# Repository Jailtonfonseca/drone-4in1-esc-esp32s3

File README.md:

# Drone — 4×ESC trifásico + ESP32-S3 na mesma PCB

> ✅ **Estado real (2026-10-12):** o board corrente é a **v10 ROTEADA** —
> [`fase3_pcb/v10/v10_roteada.kicad_pcb`](fase3_pcb/v10/v10_roteada.kicad_pcb) —
> e passa em **TODOS os gates G1–G8** do verificador
> ([`fase3_pcb/v10/verificacao_v10.txt`](fase3_pcb/v10/verificacao_v10.txt)):
> **0 curtos** (o gate novo G8 pegou 354 violações que a roteagem anterior tinha),
> 0 pads fora do contorno, 0 nets órfãs, 0 vias em keepout, 173/173 zonas preenchidas,
> 0 pads GND/VBAT_PROT sem via de stitch, ocupação elétrica 23,4 %. O pipeline de
> roteamento (FreeRouting 1.9.0) agora exporta o cobre das nets excluídas como
> **keepouts** — a placa é fabricável. Registro central de erros e correções:
> [`ERROS_CONHECIDOS.md`](ERROS_CONHECIDOS.md) (§9 = auditoria de 12/10). A BOM corrente é a
> [`orcamento/BOM_FABRICACAO_v10.csv`](orcamento/BOM_FABRICACAO_v10.csv) (MOSFET
> `NVMFS6H824NT1G`, 24 un — a BOM antiga mandava comprar o FET errado).

Projeto de **uma única PCB** que concentra: 4 inversores trifásicos (ESC), gate drivers,
sensoriamento de corrente, MCU com WiFi (ESP32-S3), IMU, barômetro, USB e toda a regulação
de energia a partir de pack LiPo 6S (25,2 V máx / 19,8 V mín).

Todo o projeto foi feito **100 % headless** nesta máquina (Linux aarch64, sem desktop):
script + CLI + PNG, com KiCad 5.1.9 via `pcbnew` (Python), ngspice 34, Icarus Verilog 11,
Yosys 0.9, gerbv 2.7.0, FreeRouting 1.9.0 (Java 17 + Xvfb) e matplotlib.

> **Regra de honestidade do projeto:** todo número afirmado nos relatórios vem de um arquivo
> de log gerado de verdade por uma ferramenta executada nesta máquina, e cada afirmação tem
> etiqueta de origem (`[MEDIDO]`, `[CALC]`, `[DATASHEET]`, `[PREMISSA]`, `[EST]`). Nada foi
> estimado "no papel" e apresentado como medido. "Pronto" é propriedade do artefato:
> [`verificacoes/verifica_projeto.py`](verificacoes/verifica_projeto.py) faz asserções duras
> e exit 1 com a lista exata do que falta.

---

## ⚠️ Status: projeto EM ANDAMENTO

| Fase | Escopo | Estado |
|---|---|---|
| 0 | Especificação e dimensionamento | ✅ concluída |
| 1 | Esquema elétrico (8 figuras) | ✅ concluída |
| 2 | Simulação SPICE + PWM em Verilog | ✅ concluída |
| 3 | PCB (6 camadas) + roteamento | ⚠️ **board v10 roteado, G1–G8 todos OK, 0 curtos** — **134/151** nets de sinal roteadas; 17 air-wires restantes (o núcleo congestionado de potência: `I_M###`, `HOM###`, `VBM###`, `LOM###`, `IMU_CS/INT`, `CC2`, `GLM103`, `UART_TX`, `VBUS_USB`) |
| 4 | Entrega: montagem, teste, riscos, regulatório | ✅ **documentação escrita** — os 4 documentos de `fase4_entrega/` existem e acompanham o envio (F14 = "já escrito", `plano/WP2_FABRICACAO.md` §1 item 11). O que falta é **executar** a bancada (G3), não escrevê-la |

**A placa v10 roteada está livre de curtos e gates verdes** — o estado
de "pronto da Fase 3" é checado por asserções duras:
[`verificacoes/verifica_projeto.py`](verificacoes/verifica_projeto.py) (SES com wires>0,
nets 100 % roteadas, G1–G8 na base E no roteado, BOM com preço em toda linha comprável).
Ele reprova exatamente no que falta — hoje: **as 17 air-wires** do núcleo de potência
(ganho marginal do autorroteador é ~1 net/30 min nesse regime; recomendação:
roteamento manual no KiCad ou revisão v11 do layout para aliviar a congestão).
Rodá-lo a qualquer momento diz onde o projeto está, sem impressão de sessão.

Para a ordem de execução completa do projeto, do estado atual até o primeiro voo —
o que falta para fabricar, o que falta para voar, a sequência de etapas, os gates e as
decisões pendentes — ver **[`PLANO_FINAL.md`](PLANO_FINAL.md)**.

### Avisos importantes

- **Nada foi validado em bancada.** Os limites de corrente contínua e o comportamento
  térmico do projeto são `[PREMISSA]` até a execução de `fase4_entrega/PLANO_TESTE_BANCADA.md`.
- **Antes de voar:** requisitos regulatórios brasileiros (registro/SISANT, peso, distância)
  precisam ser verificados — ver `fase4_entrega/SEGURANCA_E_REGULATORIO.md`.
- LiPo 6S tem energia suficiente para incêndio. Ver `fase4_entrega/RISCOS.md`.

---

## Estrutura do repositório

```
drone/
├── ERROS_CONHECIDOS.md              # registro central de erros (§9 = auditoria 12/10)
├── AUDITORIA_ERROS_2026-10-04.md    # relatório da 1a auditoria (~110 erros)
├── PROMPT_AGENTE_DRONE.md           # briefing original do projeto
├── verificacoes/                    # asserções duras de projeto (verifica_projeto.py)
├── datasheets/                      # datasheets usados (ESP32-S3-WROOM-1 etc.)
├── fase0_especificacao/             # Fase 0 — especificação
├── fase1_esquema/                   # Fase 1 — esquema elétrico (PNG + geradores Python)
├── fase2_simulacao/                 # Fase 2 — SPICE (ngspice) + Verilog (PWM/dead-time)
├── fase3_pcb/                       # Fase 3 — PCB KiCad + pipeline FreeRouting (v1 … v10)
├── fase4_entrega/                   # Fase 4 — documentação de entrega
├── orcamento/                       # Orçamento de componentes (nacional e importação)
└── plano/                           # Plano de execução — WP1..WP5, DO_PROJETO e scripts
```

### Fase 0 — Especificação (`fase0_especificacao/`)

- `FASE0_ESPECIFICACAO.md` — documento principal da especificação.
- `dimensionamento_fase0.py` / `.json` / `_saida.txt` — cálculo dos estágios.
- `verifica_limites_entrada*.py` / `verifica_limites_saida*.txt` — verificação de limites.
- `lista_componentes_fase0.csv` — **lista de componentes (43 linhas)**; é a fonte de
  quantidades do orçamento.
- `diagrama_blocos_v3.py` / `diagrama_blocos_fase0_v3.png` — diagrama de blocos.

### Fase 1 — Esquema (`fase1_esquema/`)

Oito figuras geradas por código (schemdraw), cada uma com o script que a produz:

| Figura | Assunto |
|---|---|
| `esq1_entrada_protecao.png` | Entrada, proteção e anti-inversão de polaridade |
| `esq2_buck12v.png` | Buck 12 V |
| `esq3_buck5v.png` | Buck 5 V |
| `esq4_buck3v3.png` | Buck 3,3 V |
| `esq4_esc_trifasico.png` | Ponte trifásica (uma fase) |
| `esq5_esc_halfbridge.png` | Half-bridge + gate driver |
| `esq6_esc_visao_geral.png` | Visão geral do ESC 4× |
| `esq7_mcu.png` | MCU ESP32-S3 |
| `esq8_arvore_energia.png` | Árvore de energia |

Scripts: `gera_fase1_a.py`, `gera_fase1_b.py`, `gera_fase1_c.py`, `gera_esq4.py`,
`gera_esquemas_p1.py` (rascunhos em `rascunho/`).

### Fase 2 — Simulação (`fase2_simulacao/`)

- `RESULTADOS_FASE2_SPICE.md` — relatório (uma linha por grandeza, com valor esperado,
  medido, erro e chave no log).
- `resultados_fase2_spice.csv` — a mesma tabela em CSV.
- Netlists: `buck12.cir`, `buck5.cir`, `buck3v3.cir`, `divisor_vbat.cir`, `shunt_amp.cir`,
  `gate_drive.cir`, `prot_inversao.cir`, `bemf_div.cir` (+ `.log` de cada).
- `gera_tabela.py`, `minimiza_ripple.py` — automação e otimização.
- `verilog/RELATORIO_VERILOG.md` — PWM de 12 canais com dead-time em Verilog, simulado com
  Icarus e sintetizado com Yosys.
- `_testes/` — netlists de diagnóstico usadas durante a investigação.

### Fase 3 — PCB (`fase3_pcb/`)

- `gera_pcb_v1.py` … `gera_pcb_v10.py` — geradores do board (o board é gerado por código;
  a linhagem viva é a v10 — as anteriores são registro histórico).
- `freerouting/` — pipeline de roteamento real (FreeRouting 1.9.0):
  - `dsn_export.py` — board → DSN, **com keepouts do cobre das nets excluídas** (§9.1)
    e **wires fixos** das rotas existentes (para completar roteamento parcial);
  - `ses_import.py` — SES → trilhas KiCad (com guarda anti-re-import);
  - `SesFromFrb.java` — extrai o SES de um `.frb` intermediário sem GUI (§9.6);
  - `fr_watchdog.py` — dispensa diálogos modais do FR dentro do Xvfb;
  - `FONTE_FREEROUTING.md` — o runbook: tudo medido, não presumido.
- `verifica_fase3_v10.py` → `v10/verificacao_v10.txt` — os **gates G1–G8**
  (G8 = trilha×cobre de net excluída, o gate dos 354 curtos).
- `v10/` — board base (`v10_drone.kicad_pcb`), **board roteado** (`v10_roteada.kicad_pcb`),
  SES final, logs do run e verificação.
- `verificacoes/verifica_projeto.py` (na raiz do repo) — asserções duras de projeto inteiro.
- `kicad-cli` não existe nesta máquina: os Gerbers são gerados por script `pcbnew`.

### Fase 4 — Entrega (`fase4_entrega/`)

- `PLANO_TESTE_BANCADA.md` — instrumentos e ensaios, com o que medir e critério de aceite.
- `MONTAGEM_ORDEM_DE_SOLDA.md` — ordem de solda e cuidados de montagem.
- `SEGURANCA_E_REGULATORIO.md` — segurança elétrica e requisitos regulatórios (Brasil).
- `RISCOS.md` — matriz severidade × probabilidade, mitigação e detecção.
- `ANALISE_WIFI_CONTROLE.md` — análise do link de controle WiFi.
- `calcs_fase4.txt`, `calcs_wifi_controle.txt` — saídas de cálculo usadas nos documentos.

### Orçamento (`orcamento/`)

- `ORCAMENTO.md` — relatório completo (cenário A: compra nacional; cenário B: importação).
- `orcamento_detalhado.csv` — item a item.
- `orcamento_por_bloco.csv` — agrupado por bloco funcional.
- `custo_por_bloco.png` — gráfico.
- `orcamento.py` — script que gera tudo acima.

As quantidades vêm de `fase0_especificacao/lista_componentes_fase0.csv`. Itens sem cotação
real coletada estão marcados `[EST]` no relatório.

### Plano de execução (`plano/`)

- `WP1_ROTEAMENTO.md` a `WP5_DECISOES.md` — as cinco auditorias consolidadas.
- `DO_PROJETO.md`, `mede_v7_wp1.py` — definition of done e a contagem independente do layout.
- A ordem de trabalho única está em [`PLANO_FINAL.md`](PLANO_FINAL.md), na raiz.

---

## Reproduzir

Nada aqui precisa de desktop. Exemplo:

```sh
# simulação SPICE
cd fase2_simulacao && ngspice -b buck12.cir

# board base v10 (requer KiCad 5.1 com módulo pcbnew do sistema)
cd fase3_pcb && python3.9 gera_pcb_v10.py

# pipeline de roteamento (FreeRouting 1.9.0 + Java 17 + Xvfb; ver FONTE_FREEROUTING.md)
cd fase3_pcb/freerouting && cp freerouting.json /tmp/     # o FR lê do java.io.tmpdir!
python3.9 dsn_export.py ../v10/v10_drone.kicad_pcb ../v10/freerouting_run/v10_dsn_input.dsn
xvfb-run -a java -jar <caminho>/freerouting-1.9.0.jar \
    -de ../v10/freerouting_run/v10_dsn_input.dsn -do ../v10/freerouting_run/v10_final.ses
python3.9 ses_import.py ../v10/v10_drone.kicad_pcb \
    ../v10/freerouting_run/v10_final.ses ../v10/v10_roteada.kicad_pcb

# verificação (gates G1-G8) e asserções duras de projeto
python3.9 fase3_pcb/verifica_fase3_v10.py fase3_pcb/v10/v10_roteada.kicad_pcb
python3.9 verificacoes/verifica_projeto.py

# orçamento
cd orcamento && python3.9 orcamento.py
```

## Licença

Distribuído sob a **licença MIT** — texto completo em [`LICENSE`](LICENSE).

A licença cobre todo o conteúdo do repositório: o software (scripts Python e Verilog),
os arquivos de projeto (esquemas, layout KiCad, Gerbers) e a documentação.

Como toda licença permissiva, a MIT é fornecida **"como está", sem garantia de qualquer
espécie**. Isso pesa aqui mais que o normal: este é um projeto de eletrônica de potência
**em andamento e não validado em bancada**, então a ausência de garantia e a limitação de
responsabilidade valem integralmente (ver os avisos no topo deste README).

> **Nota sobre os datasheets:** os PDFs em `datasheets/` são material de terceiros
> (Espressif, TDK/InvenSense), incluídos apenas como referência de projeto e **não**
> são cobertos pela licença MIT deste repositório.

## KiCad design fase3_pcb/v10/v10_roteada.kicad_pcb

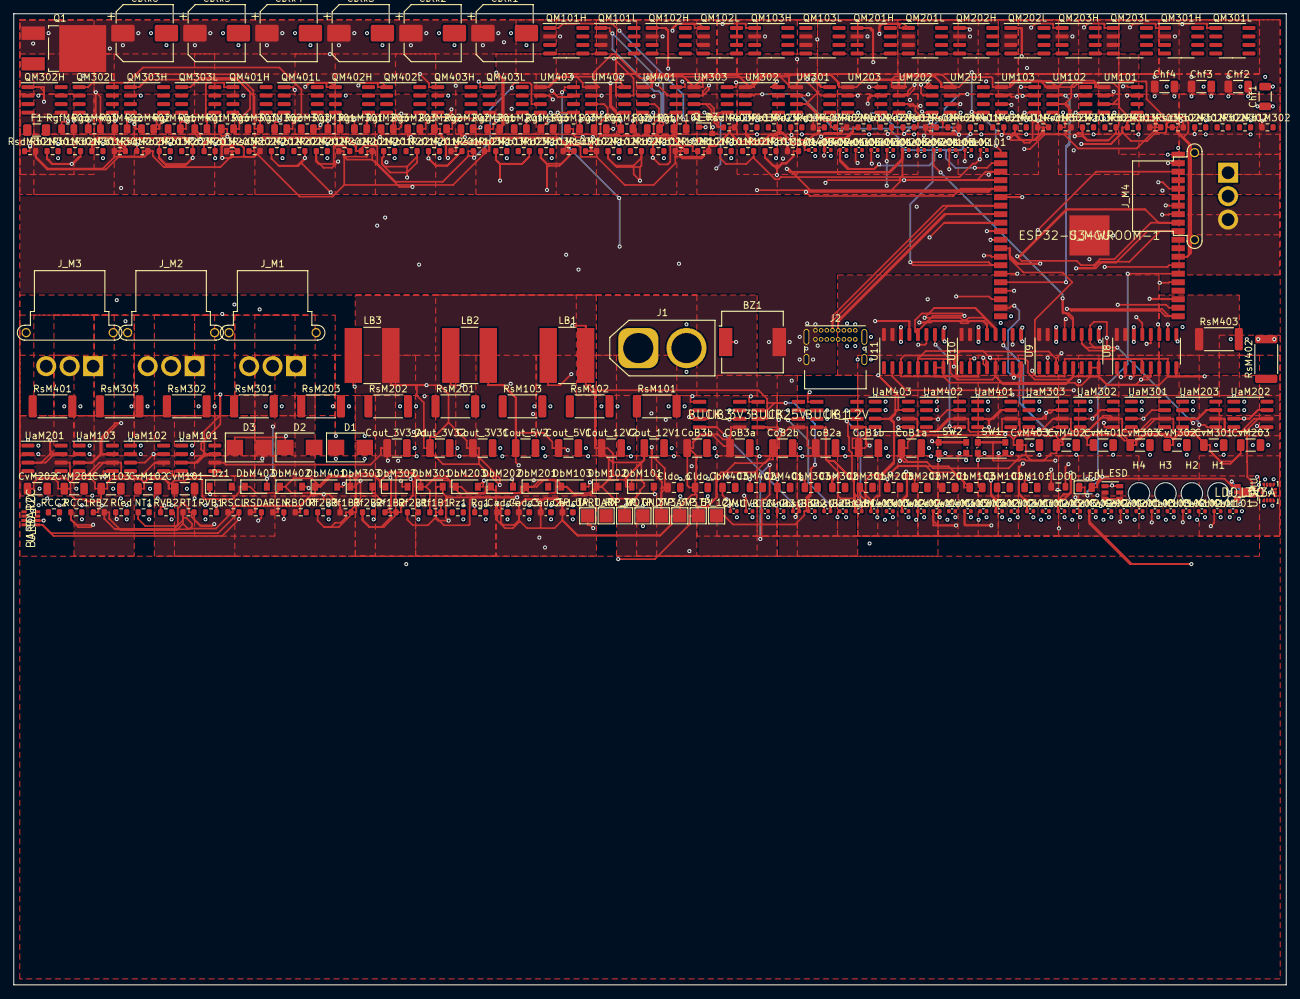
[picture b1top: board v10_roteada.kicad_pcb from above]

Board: 6 copper layers, 190.0 x 145.0 mm, 319 parts (0 on the bottom side), 179 nets.

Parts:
BZ1: Buzzer; Buzzer_CUI_CPT-9019S-SMT
CEN: C; C_0402_1005Metric
CIMU: C; C_0402_1005Metric
CVB: C; C_0402_1005Metric
CaM101, CaM102, CaM103, CaM201, CaM202, CaM203, CaM301, CaM302, CaM303, CaM401, CaM402, CaM403: C; C_0402_1005Metric
Cadc1, Cadc2, Cadc3, Cadc4: C; C_0603_1608Metric
CbM101, CbM102, CbM103, CbM201, CbM202, CbM203, CbM301, CbM302, CbM303, CbM401, CbM402, CbM403: C; C_0805_2012Metric
CbeM101, CbeM102, CbeM103, CbeM201, CbeM202, CbeM203, CbeM301, CbeM302, CbeM303, CbeM401, CbeM402, CbeM403: C; C_0402_1005Metric
Cblk1, Cblk2, Cblk3, Cblk4, Cblk5, Cblk6: CP; CP_Elec_8x10
CbstB1, CbstB2, CbstB3: C; C_0402_1005Metric
CdM101, CdM102, CdM103, CdM201, CdM202, CdM203, CdM301, CdM302, CdM303, CdM401, CdM402, CdM403: C; C_0402_1005Metric
Chf1, Chf2, Chf3, Chf4: C; C_1206_3216Metric
CinB1, CinB2, CinB3: C; C_0402_1005Metric
Cldo_i: C; C_0805_2012Metric
Cldo_o: C; C_0805_2012Metric
CoB1a, CoB1b, CoB2a, CoB2b, CoB3a, CoB3b: C; C_1210_3225Metric
Cout_3V3_A1, Cout_3V31, Cout_3V32, Cout_5V1, Cout_5V2, Cout_12V1, Cout_12V2: C; C_1210_3225Metric
CvM101, CvM102, CvM103, CvM201, CvM202, CvM203, CvM301, CvM302, CvM303, CvM401, CvM402, CvM403: C; C_1206_3216Metric
D1, D2, D3: D; D_SMB
D_LED: LED; LED_0805_2012Metric
DbM101, DbM102, DbM103, DbM201, DbM202, DbM203, DbM301, DbM302, DbM303, DbM401, DbM402, DbM403: D; D_SOD-123
Dz1: D; D_SOD-123
F1: FUSE-30A-1206; Fuse_1206_3216Metric
FLDO: L; L_0805_2012Metric
H1, H2, H3, H4: MountingHole; MountingHole_3.2mm_M3
J1: AMASS; AMASS_XT60-F_1x02_P7.20mm_Vertical
J2: USB; USB_C_Receptacle_GCT_USB4085
J_M1, J_M2, J_M3, J_M4: AMASS; AMASS_MR30PW-FB_1x03_P3.50mm_Horizontal
LB1, LB2, LB3: L; L_Bourns-SRN8040_8x8.15mm
NT1: R; R_0603_1608Metric
Q1: TO-252-2; TO-252-2_TabPin1
QM101H, QM101L, QM102H, QM102L, QM103H, QM103L, QM201H, QM201L, QM202H, QM202L, QM203H, QM203L, QM301H, QM301L, QM302H, QM302L, QM303H, QM303L, QM401H, QM401L, QM402H, QM402L, QM403H, QM403L: NVMFS6H824NT1G; SOIC-8_3.9x4.9mm_P1.27mm
Q_BZ: SOT-23
RBOOT: R; R_0603_1608Metric
RBZ: R; R_0603_1608Metric
RCC1, RCC2: R; R_0603_1608Metric
REN: R; R_0603_1608Metric
RSCL: R; R_0603_1608Metric
RSDA: R; R_0603_1608Metric
RT1: R; R_0603_1608Metric
RVB1, RVB2: R; R_0603_1608Metric
Rb1M101, Rb1M102, Rb1M103, Rb1M201, Rb1M202, Rb1M203, Rb1M301, Rb1M302, Rb1M303, Rb1M401, Rb1M402, Rb1M403, Rb2M101, Rb2M102, Rb2M103, Rb2M201, Rb2M202, Rb2M203, Rb2M301, Rb2M302, Rb2M303, Rb2M401, Rb2M402, Rb2M403: R; R_0603_1608Metric
Rd1M101, Rd1M102, Rd1M103, Rd1M201, Rd1M202, Rd1M203, Rd1M301, Rd1M302, Rd1M303, Rd1M401, Rd1M402, Rd1M403, Rd2M101, Rd2M102, Rd2M103, Rd2M201, Rd2M202, Rd2M203, Rd2M301, Rd2M302, Rd2M303, Rd2M401, Rd2M402, Rd2M403: R; R_0603_1608Metric
Rf1B1, Rf1B2, Rf1B3, Rf2B1, Rf2B2, Rf2B3: R; R_0603_1608Metric
Rg1: R; R_0603_1608Metric
RgfM101, RgfM102, RgfM103, RgfM201, RgfM202, RgfM203, RgfM301, RgfM302, RgfM303, RgfM401, RgfM402, RgfM403: R; R_0805_2012Metric
RgoM101, RgoM102, RgoM103, RgoM201, RgoM202, RgoM203, RgoM301, RgoM302, RgoM303, RgoM401, RgoM402, RgoM403: R; R_0805_2012Metric
Rled: R; R_0603_1608Metric
RsM101, RsM102, RsM103, RsM201, RsM202, RsM203, RsM301, RsM302, RsM303, RsM401, RsM402, RsM403: R; R_2512_6332Metric
RsdM101, RsdM102, RsdM103, RsdM201, RsdM202, RsdM203, RsdM301, RsdM302, RsdM303, RsdM401, RsdM402, RsdM403: R; R_0603_1608Metric
Rz1: R; R_0603_1608Metric
SW1, SW2: SW; SW_Push_1P1T_NO_CK_KMR2
TP_3V3, TP_3V3A, TP_5V, TP_12V: TestPoint; TestPoint_Pad_2.0x2.0mm
TP_GND: TestPoint; TestPoint_Pad_2.0x2.0mm
TP_UART_RX: TestPoint; TestPoint_Pad_2.0x2.0mm
TP_UART_TX: TestPoint; TestPoint_Pad_2.0x2.0mm
TP_WD: TestPoint; TestPoint_Pad_2.0x2.0mm
U8, U9, U10, U11: SOIC-16; SOIC-16_3.9x9.9mm_P1.27mm
UB1: BUCK_12V
UB2: BUCK_5V
UB3: BUCK_3V3
UM101, UM102, UM103, UM201, UM202, UM203, UM301, UM302, UM303, UM401, UM402, UM403: SOIC-8; SOIC-8_3.9x4.9mm_P1.27mm
U_BARO: BARO_I2C
U_ESD: SOT-23-6
U_IMU: LGA-14; LGA-14_3x2.5mm_P0.5mm_LayoutBorder3x4y
U_LDO: LDO_3V3A
U_MCU: ESP32-S3-WROOM-1
UaM101, UaM102, UaM103, UaM201, UaM202, UaM203, UaM301, UaM302, UaM303, UaM401, UaM402, UaM403: SOIC-8; SOIC-8_3.9x4.9mm_P1.27mm

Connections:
3V3: Cadc1.1, Cadc2.1, Cadc3.1, Cadc4.1, Cldo_i.1, CoB3a.1, CoB3b.1, Cout_3V31.1, Cout_3V32.1, D_LED.2, LB3.2, RBOOT.1, RBZ.2, REN.1, RSCL.1, RSDA.1, RT1.1, Rd1M101.1, Rd1M102.1, Rd1M103.1, Rd1M201.1, Rd1M202.1, Rd1M203.1, Rd1M301.1, Rd1M302.1, Rd1M303.1, Rd1M401.1, Rd1M402.1, Rd1M403.1, Rf1B3.1, RsdM101.2, RsdM102.2, RsdM103.2, RsdM201.2, RsdM202.2, RsdM203.2, RsdM301.2, RsdM302.2, RsdM303.2, RsdM401.2, RsdM402.2, RsdM403.2, TP_3V3.1, U8.15, U8.16, U9.15, U9.16, U10.15, U10.16, U11.15, U11.16, UB3.VCC, U_LDO.EN, U_LDO.VIN, U_MCU.2
3V3_A: Cldo_o.1, Cout_3V3_A1.1, FLDO.1, TP_3V3A.1, U_LDO.VOUT, UaM101.6, UaM102.6, UaM103.6, UaM201.6, UaM202.6, UaM203.6, UaM301.6, UaM302.6, UaM303.6, UaM401.6, UaM402.6, UaM403.6
3V3_IMU: CIMU.1, FLDO.2, U_BARO.CSB, U_BARO.VDD, U_BARO.VDDIO, U_IMU.5, U_IMU.8
5V: CoB2a.1, CoB2b.1, Cout_5V1.1, Cout_5V2.1, D3.2, LB2.2, Rf1B2.1, TP_5V.1, UB2.VCC
5V_AUX: CinB3.1, D2.1, D3.1, UB3.EN, UB3.IN
12V: CinB2.1, CoB1a.1, CoB1b.1, Cout_12V1.1, Cout_12V2.1, CvM101.1, CvM102.1, CvM103.1, CvM201.1, CvM202.1, CvM203.1, CvM301.1, CvM302.1, CvM303.1, CvM401.1, CvM402.1, CvM403.1, DbM101.1, DbM102.1, DbM103.1, DbM201.1, DbM202.1, DbM203.1, DbM301.1, DbM302.1, DbM303.1, DbM401.1, DbM402.1, DbM403.1, LB1.2, Rf1B1.1, TP_12V.1, UB1.VCC, UB2.EN, UB2.IN, UM101.1, UM102.1, UM103.1, UM201.1, UM202.1, UM203.1, UM301.1, UM302.1, UM303.1, UM401.1, UM402.1, UM403.1
ADC_CS1: U8.10, U_MCU.23
ADC_CS2: U9.10, U_MCU.15
ADC_CS3: U10.10, U_MCU.33
ADC_CS4: U11.10, U_MCU.34
BOOT_N: RBOOT.2, SW1.1, U_MCU.27
BSTB1: CbstB1.1, UB1.BST
BSTB2: CbstB2.1, UB2.BST
BSTB3: CbstB3.1, UB3.BST
BUZZER: BZ1.1, Q_BZ.1, U_MCU.16
CC1: J2.A5, RCC1.1
CC2: J2.B5, RCC2.1
EN_MCU: CEN.1, REN.2, SW2.1, U_MCU.3
FBB1: Rf1B1.2, Rf2B1.1, UB1.FB
FBB2: Rf1B2.2, Rf2B2.1, UB2.FB
FBB3: Rf1B3.2, Rf2B3.1, UB3.FB
GHM101: QM101H.1, RgoM101.2
GHM102: QM102H.1, RgoM102.2
GHM103: QM103H.1, RgoM103.2
GHM201: QM201H.1, RgoM201.2
GHM202: QM202H.1, RgoM202.2
GHM203: QM203H.1, RgoM203.2
GHM301: QM301H.1, RgoM301.2
GHM302: QM302H.1, RgoM302.2
GHM303: QM303H.1, RgoM303.2
GHM401: QM401H.1, RgoM401.2
GHM402: QM402H.1, RgoM402.2
GHM403: QM403H.1, RgoM403.2
GLM101: QM101L.1, RgfM101.2
GLM102: QM102L.1, RgfM102.2
GLM103: QM103L.1, RgfM103.2
GLM201: QM201L.1, RgfM201.2
GLM202: QM202L.1, RgfM202.2
GLM203: QM203L.1, RgfM203.2
GLM301: QM301L.1, RgfM301.2
GLM302: QM302L.1, RgfM302.2
GLM303: QM303L.1, RgfM303.2
GLM401: QM401L.1, RgfM401.2
GLM402: QM402L.1, RgfM402.2
GLM403: QM403L.1, RgfM403.2
GND: BZ1.2, CEN.2, CIMU.2, CVB.2, CaM101.2, CaM102.2, CaM103.2, CaM201.2, CaM202.2, CaM203.2, CaM301.2, CaM302.2, CaM303.2, CaM401.2, CaM402.2, CaM403.2, Cadc1.2, Cadc2.2, Cadc3.2, Cadc4.2, CbeM101.2, CbeM102.2, CbeM103.2, CbeM201.2, CbeM202.2, CbeM203.2, CbeM301.2, CbeM302.2, CbeM303.2, CbeM401.2, CbeM402.2, CbeM403.2, Cblk1.2, Cblk2.2, Cblk3.2, Cblk4.2, Cblk5.2, Cblk6.2, CdM101.2, CdM102.2, CdM103.2, CdM201.2, CdM202.2, CdM203.2, CdM301.2, CdM302.2, CdM303.2, CdM401.2, CdM402.2, CdM403.2, Chf1.2, Chf2.2, Chf3.2, Chf4.2, CinB1.2, CinB2.2, CinB3.2, Cldo_i.2, Cldo_o.2, CoB1a.2, CoB1b.2, CoB2a.2, CoB2b.2, CoB3a.2, CoB3b.2, Cout_3V3_A1.2, Cout_3V31.2, Cout_3V32.2, Cout_5V1.2, Cout_5V2.2, Cout_12V1.2, Cout_12V2.2, CvM101.2, CvM102.2, CvM103.2, CvM201.2, CvM202.2, CvM203.2, CvM301.2, CvM302.2, CvM303.2, CvM401.2, CvM402.2, CvM403.2, D1.2, J1.2, J2.A1, J2.A12, J2.B1, J2.B12, J2.S1, NT1.2, Q_BZ.2, RCC1.2, RCC2.2, RVB2.2, Rb2M101.2, Rb2M102.2, Rb2M103.2, Rb2M201.2, Rb2M202.2, Rb2M203.2, Rb2M301.2, Rb2M302.2, Rb2M303.2, Rb2M401.2, Rb2M402.2, Rb2M403.2, Rd2M101.2, Rd2M102.2, Rd2M103.2, Rd2M201.2, Rd2M202.2, Rd2M203.2, Rd2M301.2, Rd2M302.2, Rd2M303.2, Rd2M401.2, Rd2M402.2, Rd2M403.2, Rf2B1.2, Rf2B2.2, Rf2B3.2, Rg1.2, Rled.2, RsM101.2, RsM102.2, RsM103.2, RsM201.2, RsM202.2, RsM203.2, RsM301.2, RsM302.2, RsM303.2, RsM401.2, RsM402.2, RsM403.2, SW1.2, SW2.2, TP_GND.1, U8.9, U8.14, U9.9, U9.14, U10.9, U10.14, U11.9, U11.14, UB1.GND, UB2.GND, UB3.GND, UM101.4, UM102.4, UM103.4, UM201.4, UM202.4, UM203.4, UM301.4, UM302.4, UM303.4, UM401.4, UM402.4, UM403.4, U_BARO.GND, U_BARO.GND2, U_BARO.SDO, U_ESD.2, U_IMU.2, U_IMU.3, U_IMU.6, U_IMU.7, U_IMU.9, U_IMU.10, U_IMU.11, U_LDO.GND, U_MCU.1, U_MCU.40, U_MCU.41, UaM101.1, UaM101.2, UaM102.1, UaM102.2, UaM103.1, UaM103.2, UaM201.1, UaM201.2, UaM202.1, UaM202.2, UaM203.1, UaM203.2, UaM301.1, UaM301.2, UaM302.1, UaM302.2, UaM303.1, UaM303.2, UaM401.1, UaM401.2, UaM402.1, UaM402.2, UaM403.1, UaM403.2
HOM101: RgoM101.1, UM101.7
HOM102: RgoM102.1, UM102.7
HOM103: RgoM103.1, UM103.7
HOM201: RgoM201.1, UM201.7
HOM202: RgoM202.1, UM202.7
HOM203: RgoM203.1, UM203.7
HOM301: RgoM301.1, UM301.7
HOM302: RgoM302.1, UM302.7
HOM303: RgoM303.1, UM303.7
HOM401: RgoM401.1, UM401.7
HOM402: RgoM402.1, UM402.7
HOM403: RgoM403.1, UM403.7
I2C_SCL: RSCL.2, U_BARO.SCK, U_MCU.32
I2C_SDA: RSDA.2, U_BARO.SDI, U_MCU.31
IMU_CS: U_IMU.12, U_MCU.35
IMU_INT: U_IMU.4, U_MCU.24
I_M101: U8.1, UaM101.5
I_M102: U8.2, UaM102.5
I_M103: U8.3, UaM103.5
I_M201: U9.1, UaM201.5
I_M202: U9.2, UaM202.5
I_M203: U9.3, UaM203.5
I_M301: U10.1, UaM301.5
I_M302: U10.2, UaM302.5
I_M303: U10.3, UaM303.5
I_M401: U11.1, UaM401.5
I_M402: U11.2, UaM402.5
I_M403: U11.3, UaM403.5
LED_K: D_LED.1, Rled.1, U_MCU.26
LOM101: RgfM101.1, UM101.5
LOM102: RgfM102.1, UM102.5
LOM103: RgfM103.1, UM103.5
LOM201: RgfM201.1, UM201.5
LOM202: RgfM202.1, UM202.5
LOM203: RgfM203.1, UM203.5
LOM301: RgfM301.1, UM301.5
LOM302: RgfM302.1, UM302.5
LOM303: RgfM303.1, UM303.5
LOM401: RgfM401.1, UM401.5
LOM402: RgfM402.1, UM402.5
LOM403: RgfM403.1, UM403.5
PGATE: Dz1.1, Rg1.1
PHM101: CbM101.2, J_M1.1, QM101H.3, QM101L.2, Rb1M101.1, UM101.6
PHM102: CbM102.2, J_M1.2, QM102H.3, QM102L.2, Rb1M102.1, UM102.6
PHM103: CbM103.2, J_M1.3, QM103H.3, QM103L.2, Rb1M103.1, UM103.6
PHM201: CbM201.2, J_M2.1, QM201H.3, QM201L.2, Rb1M201.1, UM201.6
PHM202: CbM202.2, J_M2.2, QM202H.3, QM202L.2, Rb1M202.1, UM202.6
PHM203: CbM203.2, J_M2.3, QM203H.3, QM203L.2, Rb1M203.1, UM203.6
PHM301: CbM301.2, J_M3.1, QM301H.3, QM301L.2, Rb1M301.1, UM301.6
PHM302: CbM302.2, J_M3.2, QM302H.3, QM302L.2, Rb1M302.1, UM302.6
PHM303: CbM303.2, J_M3.3, QM303H.3, QM303L.2, Rb1M303.1, UM303.6
PHM401: CbM401.2, J_M4.1, QM401H.3, QM401L.2, Rb1M401.1, UM401.6
PHM402: CbM402.2, J_M4.2, QM402H.3, QM402L.2, Rb1M402.1, UM402.6
PHM403: CbM403.2, J_M4.3, QM403H.3, QM403L.2, Rb1M403.1, UM403.6
PWM_M101: UM101.2, U_MCU.4
PWM_M102: UM102.2, U_MCU.5
PWM_M103: UM103.2, U_MCU.6
PWM_M201: UM201.2, U_MCU.7
PWM_M202: UM202.2, U_MCU.12
PWM_M203: UM203.2, U_MCU.17
PWM_M301: UM301.2, U_MCU.18
PWM_M302: UM302.2, U_MCU.19
PWM_M303: UM303.2, U_MCU.20
PWM_M401: UM401.2, U_MCU.21
PWM_M402: UM402.2, U_MCU.22
PWM_M403: UM403.2, U_MCU.8
RB_M101: CbeM101.1, Rb1M101.2, Rb2M101.1, U8.4
RB_M102: CbeM102.1, Rb1M102.2, Rb2M102.1, U8.5
RB_M103: CbeM103.1, Rb1M103.2, Rb2M103.1, U8.6
RB_M201: CbeM201.1, Rb1M201.2, Rb2M201.1, U9.4
RB_M202: CbeM202.1, Rb1M202.2, Rb2M202.1, U9.5
RB_M203: CbeM203.1, Rb1M203.2, Rb2M203.1, U9.6
RB_M301: CbeM301.1, Rb1M301.2, Rb2M301.1, U10.4
RB_M302: CbeM302.1, Rb1M302.2, Rb2M302.1, U10.5
RB_M303: CbeM303.1, Rb1M303.2, Rb2M303.1, U10.6
RB_M401: CbeM401.1, Rb1M401.2, Rb2M401.1, U11.4
RB_M402: CbeM402.1, Rb1M402.2, Rb2M402.1, U11.5
RB_M403: CbeM403.1, Rb1M403.2, Rb2M403.1, U11.6
SD_MCU: RsdM101.1, RsdM102.1, RsdM103.1, RsdM201.1, RsdM202.1, RsdM203.1, RsdM301.1, RsdM302.1, RsdM303.1, RsdM401.1, RsdM402.1, RsdM403.1, UM101.3, UM102.3, UM103.3, UM201.3, UM202.3, UM203.3, UM301.3, UM302.3, UM303.3, UM401.3, UM402.3, UM403.3, U_MCU.28
SNM101: QM101L.3, RsM101.1, UaM101.8
SNM102: QM102L.3, RsM102.1, UaM102.8
SNM103: QM103L.3, RsM103.1, UaM103.8
SNM201: QM201L.3, RsM201.1, UaM201.8
SNM202: QM202L.3, RsM202.1, UaM202.8
SNM203: QM203L.3, RsM203.1, UaM203.8
SNM301: QM301L.3, RsM301.1, UaM301.8
SNM302: QM302L.3, RsM302.1, UaM302.8
SNM303: QM303L.3, RsM303.1, UaM303.8
SNM401: QM401L.3, RsM401.1, UaM401.8
SNM402: QM402L.3, RsM402.1, UaM402.8
SNM403: QM403L.3, RsM403.1, UaM403.8
SPI_MISO: U8.12, U9.12, U10.12, U11.12, U_IMU.1, U_MCU.11
SPI_MOSI: U8.11, U9.11, U10.11, U11.11, U_IMU.14, U_MCU.9
SPI_SCK: U8.13, U9.13, U10.13, U11.13, U_IMU.13, U_MCU.10
SWB1: CbstB1.2, LB1.1, UB1.SW
SWB2: CbstB2.2, LB2.1, UB2.SW
SWB3: CbstB3.2, LB3.1, UB3.SW
TEMP_SENSE: NT1.1, RT1.2, U_MCU.38
UART_RX: TP_UART_RX.1, U_MCU.36
UART_TX: TP_UART_TX.1, U_MCU.37
USB_DM: J2.A7, J2.B7, U_ESD.1, U_ESD.6, U_MCU.13
USB_DP: J2.A6, J2.B6, U_ESD.3, U_ESD.4, U_MCU.14
VBAT: F1.1, J1.1
VBAT_F: Dz1.2, F1.2, Q1.2, Rz1.1
VBAT_PROT: CaM101.1, CaM102.1, CaM103.1, CaM201.1, CaM202.1, CaM203.1, CaM301.1, CaM302.1, CaM303.1, CaM401.1, CaM402.1, CaM403.1, Cblk1.1, Cblk2.1, Cblk3.1, Cblk4.1, Cblk5.1, Cblk6.1, Chf1.1, Chf2.1, Chf3.1, Chf4.1, CinB1.1, D1.1, Q1.1, QM101H.2, QM102H.2, QM103H.2, QM201H.2, QM202H.2, QM203H.2, QM301H.2, QM302H.2, QM303H.2, QM401H.2, QM402H.2, QM403H.2, RVB1.1, Rz1.2, UB1.EN, UB1.IN
VBAT_SENSE: CVB.1, RVB1.2, RVB2.1, U_MCU.39
VBM101: CbM101.1, DbM101.2, UM101.8
VBM102: CbM102.1, DbM102.2, UM102.8
VBM103: CbM103.1, DbM103.2, UM103.8
VBM201: CbM201.1, DbM201.2, UM201.8
VBM202: CbM202.1, DbM202.2, UM202.8
VBM203: CbM203.1, DbM203.2, UM203.8
VBM301: CbM301.1, DbM301.2, UM301.8
VBM302: CbM302.1, DbM302.2, UM302.8
VBM303: CbM303.1, DbM303.2, UM303.8
VBM401: CbM401.1, DbM401.2, UM401.8
VBM402: CbM402.1, DbM402.2, UM402.8
VBM403: CbM403.1, DbM403.2, UM403.8
VBUS_USB: D2.2, J2.A4, J2.A9, J2.B4, J2.B9, U_ESD.5
VBZ: Q_BZ.3, RBZ.1
VREFM101: CdM101.1, Rd1M101.2, Rd2M101.1, UaM101.3, UaM101.7
VREFM102: CdM102.1, Rd1M102.2, Rd2M102.1, UaM102.3, UaM102.7
VREFM103: CdM103.1, Rd1M103.2, Rd2M103.1, UaM103.3, UaM103.7
VREFM201: CdM201.1, Rd1M201.2, Rd2M201.1, UaM201.3, UaM201.7
VREFM202: CdM202.1, Rd1M202.2, Rd2M202.1, UaM202.3, UaM202.7
VREFM203: CdM203.1, Rd1M203.2, Rd2M203.1, UaM203.3, UaM203.7
VREFM301: CdM301.1, Rd1M301.2, Rd2M301.1, UaM301.3, UaM301.7
VREFM302: CdM302.1, Rd1M302.2, Rd2M302.1, UaM302.3, UaM302.7
VREFM303: CdM303.1, Rd1M303.2, Rd2M303.1, UaM303.3, UaM303.7
VREFM401: CdM401.1, Rd1M401.2, Rd2M401.1, UaM401.3, UaM401.7
VREFM402: CdM402.1, Rd1M402.2, Rd2M402.1, UaM402.3, UaM402.7
VREFM403: CdM403.1, Rd1M403.2, Rd2M403.1, UaM403.3, UaM403.7
WD_FEED: TP_WD.1, U_MCU.25

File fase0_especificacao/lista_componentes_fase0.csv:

bloco;item;valor_especificacao;qtd;footprint_kicad_5.1;existe_no_kicad;observacao_de_compra
ENTRADA;Conector de bateria;XT60 macho+femea, 60 A [N/D offline];1;Connector_AMASS:AMASS_XT60-F_1x02_P7.20mm_Vertical;SIM;solda em furo - verificar corrente nominal no datasheet do fabricante
PROTECAO;TVS unidirecional;standoff >= 30 V, clamp ~38 V [N/D offline];1;Diode_SMD:D_SMB;SIM;comprar com Vbr acima de 25,2 V (nao conduzir em operacao)
PROTECAO;P-FET anti-inversao;canal P, Vds >= 30 V, Rds < 10 mOhm [N/D offline];1;Package_TO_SOT_SMD:TO-252-2_TabPin1;SIM;evita 3,8 W de perda que um diodo Schottky causaria (calculado)
PROTECAO;Resistor de gate do P-FET + zenner;10k + 12 V;2;Resistor_SMD:R_0603_1608Metric;SIM;clamp Vgs
BANCO;Capacitor de entrada;470 uF / 35 V polimero low-ESR;6;Capacitor_SMD:CP_Elec_8x10;SIM;ESR e' o parametro critico (<= 20 mOhm)
BANCO;Ceramico de alta freq.;10 uF / 50 V X7R;12;Capacitor_SMD:C_1206_3216Metric;SIM;1 por par de MOSFET
BANCO;Ceramico de alta freq.;100 nF / 50 V X7R;48;Capacitor_SMD:C_0402_1005Metric;SIM;colado ao par (loop minimo)
POTENCIA;MOSFET N;Vds >= 40 V, Rds <= 3 mOhm @10V, Qg <= 60 nC [PREMISSA];24;Package_TO_SOT_SMD:TO-252-3_TabPin2;SIM;24 unidades = 4 motores x 6; alternativa PowerPAK 5x6 se couber
POTENCIA;Dissipador / area de cobre;2 oz, poligono no dreno;-;GERADO NO LAYOUT;N/A;temperatura e' decidida no PCB (Rth_ja)
GATE DRIVE;Driver half-bridge single-input;bootstrap, dead-time interno ~520 ns, Vcc 12 V [N/D offline];12;Package_SO:SOIC-8_3.9x4.9mm_P1.27mm;SIM;1 por half-bridge; exige entrada unica p/ caber em 12 PWMs
GATE DRIVE;Resistor de gate;10 ohm (Rg >= 2*Z0 = 6,3 ohm calculado);24;Resistor_SMD:R_0805_2012Metric;SIM;valores 4,7-22 ohm para ajuste em bancada
GATE DRIVE;Resistor de gate (desliga);2,2 ohm;24;Resistor_SMD:R_0805_2012Metric;SIM;opcional: turn-off mais rapido + diodo
GATE DRIVE;Capacitor de bootstrap;1 uF / 25 V X7R (>= 20*Qg calculado);12;Capacitor_SMD:C_0805_2012Metric;SIM;queda calculada 40 mV por ciclo
GATE DRIVE;Diodo de bootstrap;ultrarrapido 100 V / 1 A [N/D offline];12;Diode_SMD:D_SOD-123;SIM;
GATE DRIVE;Capacitor local do driver;10 uF / 25 V X7R;12;Capacitor_SMD:C_1206_3216Metric;SIM;fornece a corrente de pico de gate (1,2 A calculado)
CORRENTE;Shunt de fase;0,5 mOhm 2 W 2512 manganina (112 mW continuo calculado);12;Resistor_SMD:R_2512_6332Metric;SIM;3 por motor
CORRENTE;Amplificador diferencial;ganho 50, CMVR >= 30 V, largura de banda >= 400 kHz [N/D offline];12;Package_SO:SOIC-8-1EP_3.9x4.9mm_EP2.41x3.81mm;SIM;1 por shunt; saida centrada em 1,65 V
CORRENTE;Divisor de referencia;10k/10k 1% + 100 nF;12;Resistor_SMD:R_0603_1608Metric;SIM;gera 1,65 V de offset
BEMF;Divisor de fase;8,2k/1,0k 1% (25,2 V -> 2,74 V calculado);12;Resistor_SMD:R_0603_1608Metric;SIM;3 por motor [FIX auditoria 3: 25,2 V x 1,0k/9,2k = 2,74 V; o valor anterior de 3,07 V usava so' os 8,2k no divisor]
BEMF;Filtro + clamp;1 nF + diodo clamp 3,3 V / zenner;12;Capacitor_SMD:C_0402_1005Metric;SIM;
ADC;ADC externo SPI;16 canais, >= 200 ksps, 12 bits [N/D offline];1;Package_DFN_QFN / Package_SO conforme CI;SIM (generico);obrigatorio: ADC do ESP32 nao cobre 26 canais (calculado)
ADC;Mux analogico (se usar 2x CI de 8 canais);[N/D offline];2;Package_SO:SOIC-16;SIM (generico);alternativa ao ADC de 16 canais
MCU;Modulo ESP32-S3-WROOM-1;WiFi 2,4 GHz + USB nativo;1;NAO EXISTE NO KICAD 5.1 - GERAR POR SCRIPT;NAO;preciso do mechanical drawing p/ gerar a pegada (41 pads castelados)
MCU;Botao BOOT + EN;tatico 2 pinos;2;Button_SMD / SW_SPST;SIM;
MCU;Pull-ups de I2C;4,7k;2;Resistor_SMD:R_0603_1608Metric;SIM;
MCU;Pads de programacao;UART0 TX/RX + pads 1,27 mm;-;TestPoint:TestPoint_Loop_D2.50mm_Drill1.0mm;SIM;
IMU;IMU 6 eixos;SPI/I2C, QFN-24 3x3 [confirmar CI exato];1;Sensor_Motion:InvenSense_QFN-24_3x3mm_P0.4mm;SIM (generico);datasheet nao disponivel offline
BAROMETRO;Barometro;I2C, LGA-8;1;NAO EXISTE - GERAR LGA-8;NAO;nao ha pegada no KiCad 5.1
ENERGIA;Buck 12 V;0,60 A, L=89 uH, Cout=2x22 uF (calculado);1;Inductor_SMD:L_12x12mm_H6mm;SIM;alimenta os 12 gate drivers (49 mA calculado)
ENERGIA;Buck 5 V;2,00 A, L=17 uH, Cout=2x22 uF (calculado);1;Inductor_SMD:L_Bourns_SRR1210A;SIM;
ENERGIA;Buck 3,3 V;1,50 A, L=5 uH, Cout=2x22 uF (calculado);1;Inductor_SMD:L_Bourns-SRN8040_8x8.15mm;SIM;entrada vinda do trilho de 5 V
ENERGIA;LDO 3,3 V_A;150 mA, baixo ruido (Pdiss 255 mW calculado);1;Package_TO_SOT_SMD:SOT-23;SIM;analogico: IMU + barometro
ENERGIA;Indutor de saida;22 uH (12 V e 5 V) / 5 uH (3,3 V);3;Inductor_SMD:L_12x12mm_H6mm;SIM;corrente de saturacao >= 2x a nominal
ENERGIA;Capacitor de saida;22 uF / 25 V X7R;6;Capacitor_SMD:C_1210;SIM;2 por buck
MOTOR;Conector de motor;MR30 3 pinos (fases U/V/W);4;Connector_AMASS:AMASS_MR30PW-FB_1x03_P3.50mm_Horizontal;SIM;alternativa: bloco terminal 3,5 mm
USB;Receptaculo USB-C;16 pinos, so' programacao;1;Connector_USB:USB_C_Receptacle_GCT_USB4085;SIM;com protecao ESD e ideal diode
USB;Protecao ESD USB;array ESD [N/D offline];1;Package_SO:SOT-23-6;SIM;
USB;Ideal diode do VBUS;P-FET + controlador [N/D offline];1;Package_TO_SOT_SMD:SOT-23-6;SIM;permite alimentar a placa sem bateria
EXTRA;LED de status;verde 0805 + resistor 1k;1;LED_SMD:LED_0805_2012Metric;SIM;
EXTRA;Buzzer;SMD 4 kHz;1;Buzzer:Buzzer_CUI_CPT-9019S-SMT;SIM;com transistor de acionamento
EXTRA;Watchdog externo (opcional);corte de motores independente do firmware;1;Package_SO:SOIC-8;SIM (generico);recomendado para failsafe
EXTRA;Fusivel/e-fuse de entrada;30 A [N/D offline];1;Fuse:Fuse_1206;SIM;recomendado - decisao pendente do Jailton
MECANICO;PCB;4 camadas, 2 oz nas externas, ~40x60 mm (estimativa);1;GERADO NA FASE 3;N/A;tamanho definido no layout

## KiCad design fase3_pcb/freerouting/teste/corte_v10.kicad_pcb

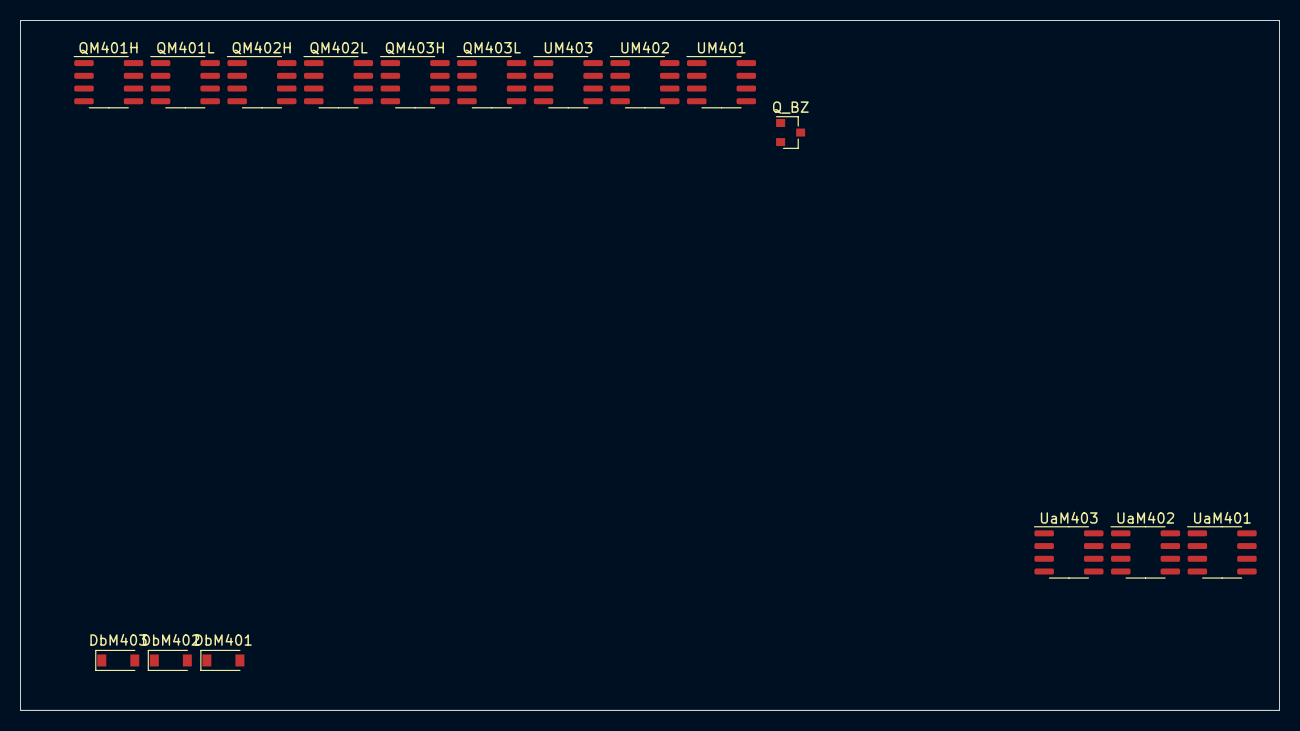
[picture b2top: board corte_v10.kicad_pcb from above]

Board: 6 copper layers, 125.7 x 68.9 mm, 16 parts (0 on the bottom side), 17 nets, no tracks yet.

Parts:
DbM401, DbM402, DbM403: D; D_SOD-123
QM401H, QM401L, QM402H, QM402L, QM403H, QM403L: NVMFS6H824NT1G; SOIC-8_3.9x4.9mm_P1.27mm
Q_BZ: SOT-23
UM401, UM402, UM403: SOIC-8; SOIC-8_3.9x4.9mm_P1.27mm
UaM401, UaM402, UaM403: SOIC-8; SOIC-8_3.9x4.9mm_P1.27mm

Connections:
3V3_A: UaM401.6, UaM402.6, UaM403.6
12V: DbM401.1, DbM402.1, DbM403.1, UM401.1, UM402.1, UM403.1
GND: Q_BZ.2, UM401.4, UM402.4, UM403.4, UaM401.1, UaM401.2, UaM402.1, UaM402.2, UaM403.1, UaM403.2
PHM401: QM401H.3, QM401L.2, UM401.6
PHM402: QM402H.3, QM402L.2, UM402.6
PHM403: QM403H.3, QM403L.2, UM403.6
SD_MCU: UM401.3, UM402.3, UM403.3
SNM401: QM401L.3, UaM401.8
SNM402: QM402L.3, UaM402.8
SNM403: QM403L.3, UaM403.8
VBAT_PROT: QM401H.2, QM402H.2, QM403H.2
VBM401: DbM401.2, UM401.8
VBM402: DbM402.2, UM402.8
VBM403: DbM403.2, UM403.8
VREFM401: UaM401.3, UaM401.7
VREFM402: UaM402.3, UaM402.7
VREFM403: UaM403.3, UaM403.7

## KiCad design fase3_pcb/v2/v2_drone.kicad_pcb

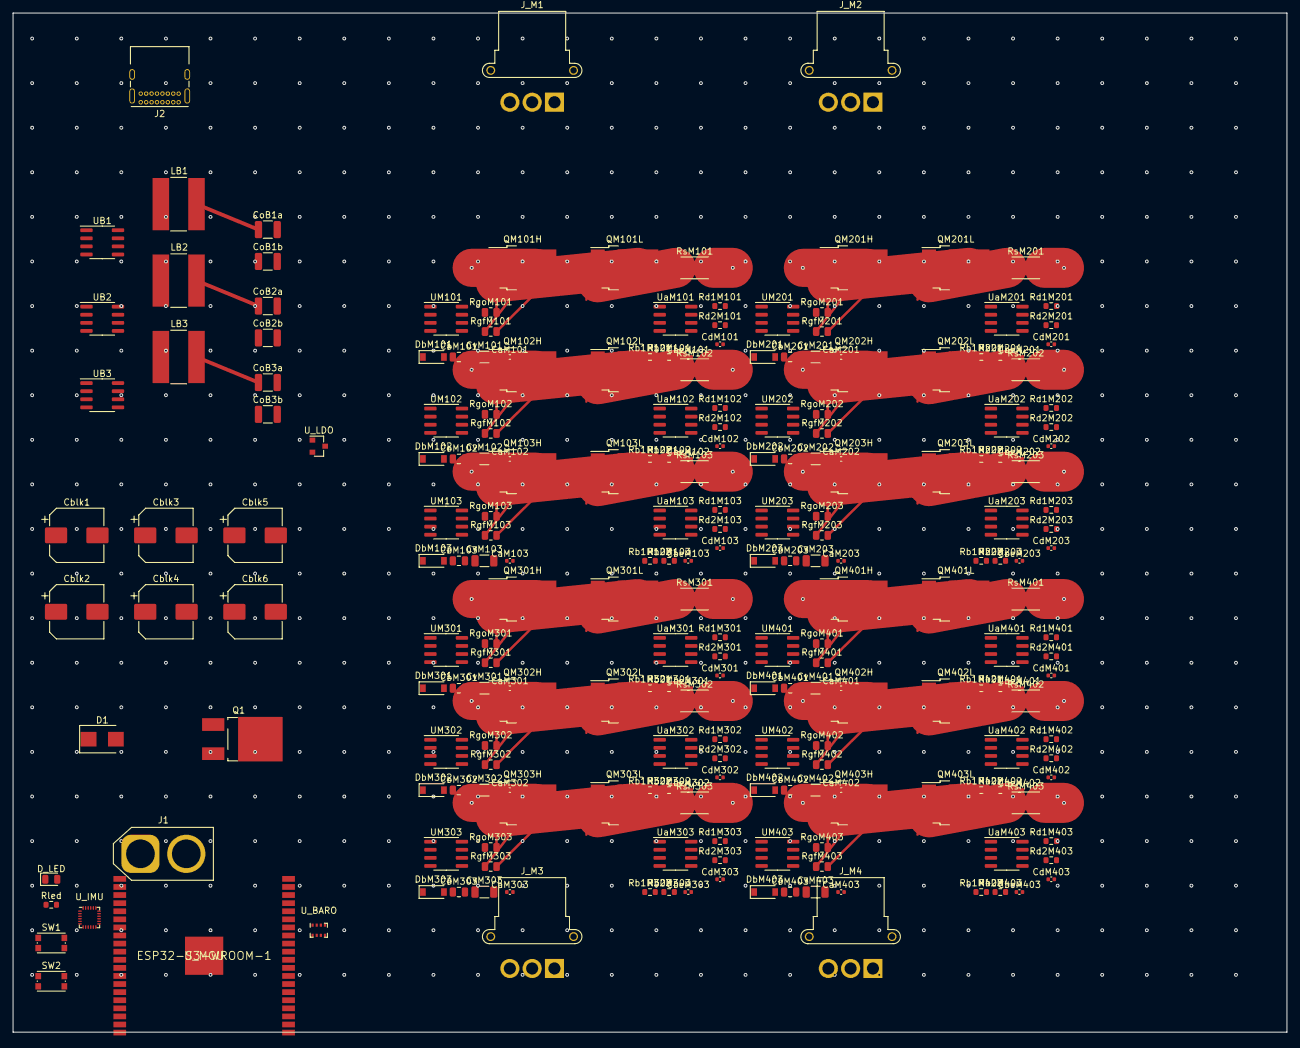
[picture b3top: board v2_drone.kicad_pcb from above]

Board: 4 copper layers, 200.0 x 160.0 mm, 238 parts (0 on the bottom side), 56 nets.

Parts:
CaM101, CaM102, CaM103, CaM201, CaM202, CaM203, CaM301, CaM302, CaM303, CaM401, CaM402, CaM403: C_0402_1005Metric
CbM101, CbM102, CbM103, CbM201, CbM202, CbM203, CbM301, CbM302, CbM303, CbM401, CbM402, CbM403: C_0805_2012Metric
CbeM101, CbeM102, CbeM103, CbeM201, CbeM202, CbeM203, CbeM301, CbeM302, CbeM303, CbeM401, CbeM402, CbeM403: C_0402_1005Metric
Cblk1, Cblk2, Cblk3, Cblk4, Cblk5, Cblk6: CP_Elec_8x10
CdM101, CdM102, CdM103, CdM201, CdM202, CdM203, CdM301, CdM302, CdM303, CdM401, CdM402, CdM403: C_0402_1005Metric
CoB1a, CoB1b, CoB2a, CoB2b, CoB3a, CoB3b: C_1210_3225Metric
CvM101, CvM102, CvM103, CvM201, CvM202, CvM203, CvM301, CvM302, CvM303, CvM401, CvM402, CvM403: C_1206_3216Metric
D1: D_SMB
D_LED: LED_0805_2012Metric
DbM101, DbM102, DbM103, DbM201, DbM202, DbM203, DbM301, DbM302, DbM303, DbM401, DbM402, DbM403: D_SOD-123
J1: AMASS_XT60-F_1x02_P7.20mm_Vertical
J2: USB_C_Receptacle_GCT_USB4085
J_M1, J_M2, J_M3, J_M4: AMASS_MR30PW-FB_1x03_P3.50mm_Horizontal
LB1, LB2, LB3: L_Bourns-SRN8040_8x8.15mm
Q1: TO-252-2_TabPin1
QM101H, QM101L, QM102H, QM102L, QM103H, QM103L, QM201H, QM201L, QM202H, QM202L, QM203H, QM203L, QM301H, QM301L, QM302H, QM302L, QM303H, QM303L, QM401H, QM401L, QM402H, QM402L, QM403H, QM403L: TO-252-3_TabPin2
Rb1M101, Rb1M102, Rb1M103, Rb1M201, Rb1M202, Rb1M203, Rb1M301, Rb1M302, Rb1M303, Rb1M401, Rb1M402, Rb1M403, Rb2M101, Rb2M102, Rb2M103, Rb2M201, Rb2M202, Rb2M203, Rb2M301, Rb2M302, Rb2M303, Rb2M401, Rb2M402, Rb2M403: R_0603_1608Metric
Rd1M101, Rd1M102, Rd1M103, Rd1M201, Rd1M202, Rd1M203, Rd1M301, Rd1M302, Rd1M303, Rd1M401, Rd1M402, Rd1M403, Rd2M101, Rd2M102, Rd2M103, Rd2M201, Rd2M202, Rd2M203, Rd2M301, Rd2M302, Rd2M303, Rd2M401, Rd2M402, Rd2M403: R_0603_1608Metric
RgfM101, RgfM102, RgfM103, RgfM201, RgfM202, RgfM203, RgfM301, RgfM302, RgfM303, RgfM401, RgfM402, RgfM403: R_0805_2012Metric
RgoM101, RgoM102, RgoM103, RgoM201, RgoM202, RgoM203, RgoM301, RgoM302, RgoM303, RgoM401, RgoM402, RgoM403: R_0805_2012Metric
Rled: R_0603_1608Metric
RsM101, RsM102, RsM103, RsM201, RsM202, RsM203, RsM301, RsM302, RsM303, RsM401, RsM402, RsM403: R_2512_6332Metric
SW1, SW2: SW_Push_1P1T_NO_CK_KMR2
UB1, UB2, UB3: SOIC-8_3.9x4.9mm_P1.27mm
UM101, UM102, UM103, UM201, UM202, UM203, UM301, UM302, UM303, UM401, UM402, UM403: SOIC-8_3.9x4.9mm_P1.27mm
U_BARO: Bosch_LGA-8_2x2.5mm_P0.65mm_ClockwisePinNumbering
U_IMU: InvenSense_QFN-24_3x3mm_P0.4mm
U_LDO: SOT-23
U_MCU: ESP32-S3-WROOM-1
UaM101, UaM102, UaM103, UaM201, UaM202, UaM203, UaM301, UaM302, UaM303, UaM401, UaM402, UaM403: SOIC-8_3.9x4.9mm_P1.27mm

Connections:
3V3: CoB3a.1, CoB3b.1, D_LED.2, LB3.2, U_LDO.3
5V: CoB2a.1, CoB2b.1, LB2.2
12V: CoB1a.1, CoB1b.1, CvM101.1, CvM102.1, CvM103.1, CvM201.1, CvM202.1, CvM203.1, CvM301.1, CvM302.1, CvM303.1, CvM401.1, CvM402.1, CvM403.1, DbM101.1, DbM102.1, DbM103.1, DbM201.1, DbM202.1, DbM203.1, DbM301.1, DbM302.1, DbM303.1, DbM401.1, DbM402.1, DbM403.1, LB1.2
GHM101: QM101H.1, RgfM101.2, RgoM101.2
GHM102: QM102H.1, RgfM102.2, RgoM102.2
GHM103: QM103H.1, RgfM103.2, RgoM103.2
GHM201: QM201H.1, RgfM201.2, RgoM201.2
GHM202: QM202H.1, RgfM202.2, RgoM202.2
GHM203: QM203H.1, RgfM203.2, RgoM203.2
GHM301: QM301H.1, RgfM301.2, RgoM301.2
GHM302: QM302H.1, RgfM302.2, RgoM302.2
GHM303: QM303H.1, RgfM303.2, RgoM303.2
GHM401: QM401H.1, RgfM401.2, RgoM401.2
GHM402: QM402H.1, RgfM402.2, RgoM402.2
GHM403: QM403H.1, RgfM403.2, RgoM403.2
GND: CaM101.2, CaM102.2, CaM103.2, CaM201.2, CaM202.2, CaM203.2, CaM301.2, CaM302.2, CaM303.2, CaM401.2, CaM402.2, CaM403.2, CbeM101.2, CbeM102.2, CbeM103.2, CbeM201.2, CbeM202.2, CbeM203.2, CbeM301.2, CbeM302.2, CbeM303.2, CbeM401.2, CbeM402.2, CbeM403.2, Cblk1.2, Cblk2.2, Cblk3.2, Cblk4.2, Cblk5.2, Cblk6.2, CdM101.2, CdM102.2, CdM103.2, CdM201.2, CdM202.2, CdM203.2, CdM301.2, CdM302.2, CdM303.2, CdM401.2, CdM402.2, CdM403.2, CoB1a.2, CoB1b.2, CoB2a.2, CoB2b.2, CoB3a.2, CoB3b.2, CvM101.2, CvM102.2, CvM103.2, CvM201.2, CvM202.2, CvM203.2, CvM301.2, CvM302.2, CvM303.2, CvM401.2, CvM402.2, CvM403.2, D1.2, J1.2, Rb2M101.2, Rb2M102.2, Rb2M103.2, Rb2M201.2, Rb2M202.2, Rb2M203.2, Rb2M301.2, Rb2M302.2, Rb2M303.2, Rb2M401.2, Rb2M402.2, Rb2M403.2, Rled.2, RsM101.2, RsM102.2, RsM103.2, RsM201.2, RsM202.2, RsM203.2, RsM301.2, RsM302.2, RsM303.2, RsM401.2, RsM402.2, RsM403.2, U_LDO.2
LED_K: D_LED.1, Rled.1
PHM101: CbM101.2, QM101H.3, QM101L.2, Rb1M101.1
PHM102: CbM102.2, QM102H.3, QM102L.2, Rb1M102.1
PHM103: CbM103.2, QM103H.3, QM103L.2, Rb1M103.1
PHM201: CbM201.2, QM201H.3, QM201L.2, Rb1M201.1
PHM202: CbM202.2, QM202H.3, QM202L.2, Rb1M202.1
PHM203: CbM203.2, QM203H.3, QM203L.2, Rb1M203.1
PHM301: CbM301.2, QM301H.3, QM301L.2, Rb1M301.1
PHM302: CbM302.2, QM302H.3, QM302L.2, Rb1M302.1
PHM303: CbM303.2, QM303H.3, QM303L.2, Rb1M303.1
PHM401: CbM401.2, QM401H.3, QM401L.2, Rb1M401.1
PHM402: CbM402.2, QM402H.3, QM402L.2, Rb1M402.1
PHM403: CbM403.2, QM403H.3, QM403L.2, Rb1M403.1
SNM101: QM101L.3, RsM101.1
SNM102: QM102L.3, RsM102.1
SNM103: QM103L.3, RsM103.1
SNM201: QM201L.3, RsM201.1
SNM202: QM202L.3, RsM202.1
SNM203: QM203L.3, RsM203.1
SNM301: QM301L.3, RsM301.1
SNM302: QM302L.3, RsM302.1
SNM303: QM303L.3, RsM303.1
SNM401: QM401L.3, RsM401.1
SNM402: QM402L.3, RsM402.1
SNM403: QM403L.3, RsM403.1
VBAT: CaM101.1, CaM102.1, CaM103.1, CaM201.1, CaM202.1, CaM203.1, CaM301.1, CaM302.1, CaM303.1, CaM401.1, CaM402.1, CaM403.1, J1.1, Q1.1, QM101H.2, QM102H.2, QM103H.2, QM201H.2, QM202H.2, QM203H.2, QM301H.2, QM302H.2, QM303H.2, QM401H.2, QM402H.2, QM403H.2
VBAT_PROT: Cblk1.1, Cblk2.1, Cblk3.1, Cblk4.1, Cblk5.1, Cblk6.1, D1.1, Q1.2
VBM101: CbM101.1, DbM101.2
VBM102: CbM102.1, DbM102.2
VBM103: CbM103.1, DbM103.2
VBM201: CbM201.1, DbM201.2
VBM202: CbM202.1, DbM202.2
VBM203: CbM203.1, DbM203.2
VBM301: CbM301.1, DbM301.2
VBM302: CbM302.1, DbM302.2
VBM303: CbM303.1, DbM303.2
VBM401: CbM401.1, DbM401.2
VBM402: CbM402.1, DbM402.2
VBM403: CbM403.1, DbM403.2
VREF: CdM101.1, CdM102.1, CdM103.1, CdM201.1, CdM202.1, CdM203.1, CdM301.1, CdM302.1, CdM303.1, CdM401.1, CdM402.1, CdM403.1, Rd1M101.1, Rd1M102.1, Rd1M103.1, Rd1M201.1, Rd1M202.1, Rd1M203.1, Rd1M301.1, Rd1M302.1, Rd1M303.1, Rd1M401.1, Rd1M402.1, Rd1M403.1, Rd2M101.1, Rd2M102.1, Rd2M103.1, Rd2M201.1, Rd2M202.1, Rd2M203.1, Rd2M301.1, Rd2M302.1, Rd2M303.1, Rd2M401.1, Rd2M402.1, Rd2M403.1
